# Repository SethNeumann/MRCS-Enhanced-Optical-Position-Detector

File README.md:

# REPO NAME: MRCS-Enhanced-Optical-Position-Detector
## License: Creative Commons Attribution-NonCommercial-ShareAlike

Optical Position Detectors are useful when precise position detection is required (clearing a staging throat, for example), 
when the area to be detected is small (an "OS" section in a CTC system) or where resistance wheel sets cannot be applied 
and current detection can't be used.  The Enhanced Optical Position Detector is based on Geoff Bunza's DAPD and provides a 
fixed turn-on and turn-off delay and high power output stage similar to Bruce Chubb's DCC-OD (so if you need an optical 
detector that's electrically compatible with a cpOD or DCC-OD, EOPD is for you!).

The EOPD uses Geoff's self-calibrating detection circuit, so you don't need to adjust for ambient light level.  Note the 
circuit won't work in the dark unless you substitute infrared Photo transistors and provide an infrared illumination source.  
The supply voltage range is 5-15 volts and the output is a negative-true open collector which will sink up to 600 mA at up 
to 40VDC.  Size is 1.15" x 1.75 x 0.5" high"

Either 2 PT-19 photo transistors or “Da Fingah” are provided. a reference and another to be placed between the rails. You may
solder the reference onto the board if the board will be mounted where is has the same illumination as the track or both may be mounted remotely.

The EOPD is a compatible Modular Signaling System (MSS) Optical Detector

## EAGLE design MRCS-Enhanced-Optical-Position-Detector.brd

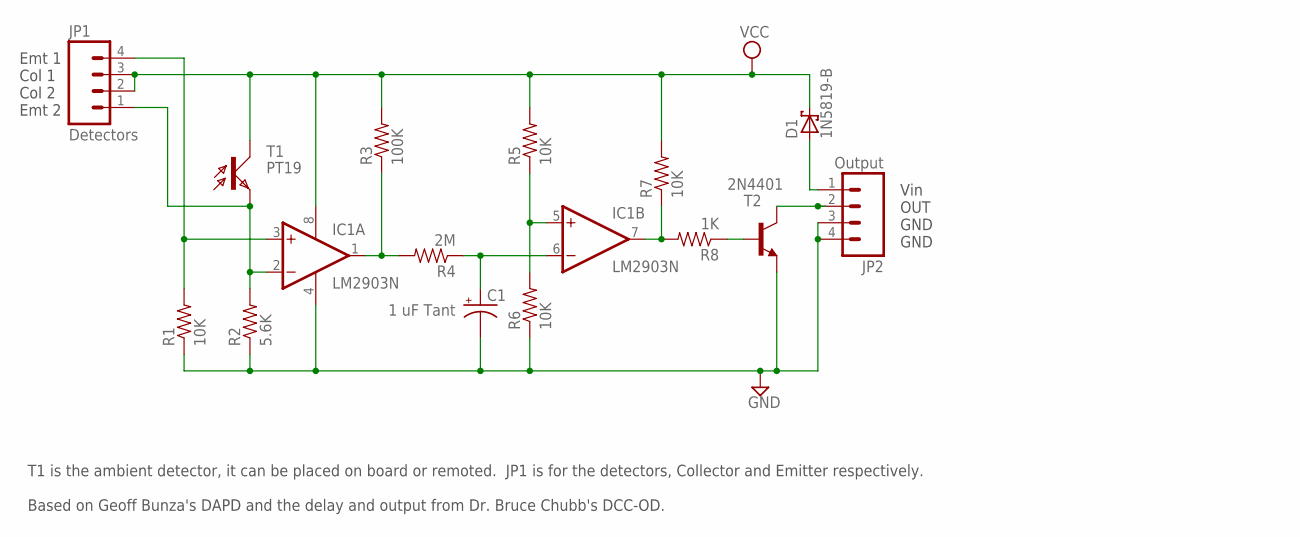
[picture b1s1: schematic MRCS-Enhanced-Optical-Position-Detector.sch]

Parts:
C1: 1 uF Tant; E2,5-5
D1: 1N5819-B; DO41-7.6
IC1: LM2903N; DIL08
JP1: Detectors; 1X04_LOCK
JP2: Output; 1X04_LOCK
R1, R5, R6, R7: 10K; AXIAL-0.4
R2: 5.6K; AXIAL-0.4
R3: 100K; AXIAL-0.4
R4: 2M; AXIAL-0.4
R8: 1K; AXIAL-0.4
T1: PT19; BPX81
T2: 2N4401; TO92-EBC

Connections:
GND: C1.-, IC1.4 (V-), JP2.3, JP2.4, R1.P$1 (1), R2.P$1 (1), R6.P$1 (1), T2.E
unnamed: IC1.2 (-IN), JP1.1, R2.P$2 (2), T1.E
unnamed: C1.+, IC1.6 (-IN), R4.P$1 (1)
unnamed: IC1.3 (+IN), JP1.4, R1.P$2 (2)
unnamed: IC1.1 (OUT), R3.P$1 (1), R4.P$2 (2)
unnamed: IC1.7 (OUT), R7.P$1 (1), R8.P$2 (2)
unnamed: IC1.5 (+IN), R5.P$1 (1), R6.P$2 (2)
unnamed: R8.P$1 (1), T2.B
unnamed: JP2.2, T2.C
VCC: D1.C, IC1.8 (V+), JP1.2, JP1.3, R3.P$2 (2), R5.P$2 (2), R7.P$2 (2), T1.C
VIN: D1.A, JP2.1

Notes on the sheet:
Vin OUT GND GND
Emt 1 Col 1 Col 2 Emt 2
T1 is the ambient detector, it can be placed on board or remoted. JP1 is for the detectors, Collector and Emitter respectively. Based on Geoff Bunza's DAPD and the delay and output from Dr. Bruce Chubb's DCC-OD.

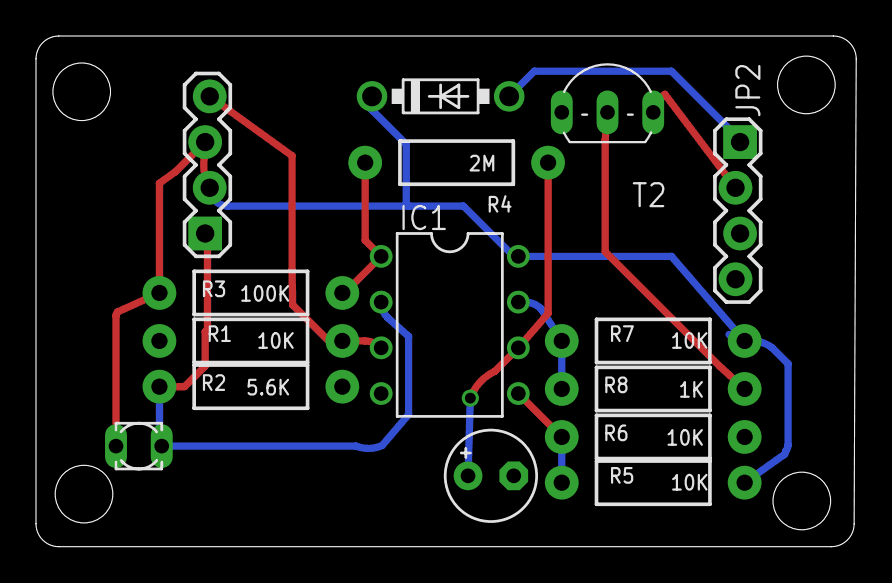
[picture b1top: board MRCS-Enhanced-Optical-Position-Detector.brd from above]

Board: 2 copper layers, 45.6 x 28.4 mm, 17 parts (0 on the bottom side), 11 nets.

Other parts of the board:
U$1: MRCSLOGOBTM
U$3: CA-PROP65WARNING

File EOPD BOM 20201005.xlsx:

Qty | Value | Device | Package | Parts | Description | Vendor | Part | Unit | Extd | EOQ
1 | 1 uF Tant | CPOL-USE2.5-5 | E2,5-5 | C1 | POLARIZED CAPACITOR, Tant | Jameco | 1938421 | 0.28999999999999998 | 0.28999999999999998 | 10
1 | 1N5819 | Schottky diode, 1A 40V | DO41 | D1 | Schottky diode, 1A 40V | Jameco | 177965 | 0.25 | 0.25 | 10
4 | 10K | RESISTORPTH-1/4W | AXIAL-0.4 | R1, R5, R6, R7 | Resistor | Jameco | 691104 | 0.04 | 0.16 | 100
1 | 100K | RESISTORPTH-1/4W | AXIAL-0.4 | R3 | Resistor | Jameco | 691340 | 0.04 | 0.04 | 100
1 | 1K | RESISTORPTH-1/4W | AXIAL-0.4 | R8 | Resistor | Jameco | 690865 | 0.04 | 0.04 | 100
1 | 2M | RESISTORPTH-1/4W | AXIAL-0.4 | R4 | Resistor | Jameco | 691649 | 0.04 | 0.04 | 100
1 | 5.6K | RESISTORPTH-1/4W | AXIAL-0.4 | R2 | Resistor | Jameco | 691041 | 0.04 | 0.04 | 100
1 | 1N5819 | Diode Shottky 1N5819 | Jameco | D1 | Diode Shottky 1N5819 | Jameco | 177965 | 0.14000000000000001 | 0.14000000000000001 | 100
1 | 2N4401 | 2N4401 | TO92-EBC | T2 | NPN Transistor | Jameco | 38421 | 0.06 | 0.06 | 100
2 | 4 pos screw | 4 position Screw terminal | 1X04_LOCK | JP1,2 | 4 position Screw terminal | electronic salon |  | 0.4 | 0.8 | 100
1 | LM2903N | LM2903N | DIL08 | IC1 | COMPARATOR | Jameco | 1922939 | 0.25 | 0.25 | 10
1 | PCB | EOPD | PCB | PCB | EOPD | Seeed |  | 1.03 | 1.03 | 10
 |  |  |  |  |  |  | Unit total |  | 3.1400000000000006
 |  |  |  |  |  |  | Parts Markup | 0.2 | 0.62800000000000011
 |  |  |  |  |  |  | Parts |  | 3.7680000000000007
8 |  | minutes |  |  |  |  | Labor | 1 | 8 |  | inovice 28921
 |  |  |  |  |  |  | Labor Markup | 0.2 | 1.6
 |  |  |  |  |  |  | Labor |  | 9.6
 |  |  |  |  |  |  | Parts + Labor |  | 13.368
 |  |  |  |  |  |  | Ecommerce | 0.1 | 1.3368000000000002
 |  |  |  |  |  |  | Grand Total |  | 14.704800000000001
 |  |  |  |  |  |  | Sell |  | 15
2 |  | PT19 | TO92 | Option + T1 | Photo transistor | Digikey | 1080-1019-ND |  | 0.26 | 50

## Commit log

2020-10-06 intial commit
2020-10-06 initial commit
    imported from old Eagle project directory
2020-11-21 clean up before panelizing
    miscellaneous clean up of the file preperatory to panelizing
2020-12-20 changes for legibility and work file cleanup
    cleaned out work and derivative files
2020-12-24 added some work files to gitignore so as not to confuse
    various work files for documentation
2020-12-29 Final documentation of EOPD
    added tables of test voltages, clean up, rebuilt TOC and tables of figures, tables
2020-12-29 Update EOPD Rev_1.pdf
    printed the whole doc, not just 1st page
2021-01-06 Added values for no-delay
    Values for no-delay version

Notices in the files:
parts and their libraries:
SparkFun-Connectors: Licensing: Creative Commons ShareAlike 4.0 International - https://creativecommons.org/licenses/by-sa/4.0
SparkFun-Resistors: Licensing: CC v3.0 Share-Alike You are welcome to use this library for commercial purposes.
